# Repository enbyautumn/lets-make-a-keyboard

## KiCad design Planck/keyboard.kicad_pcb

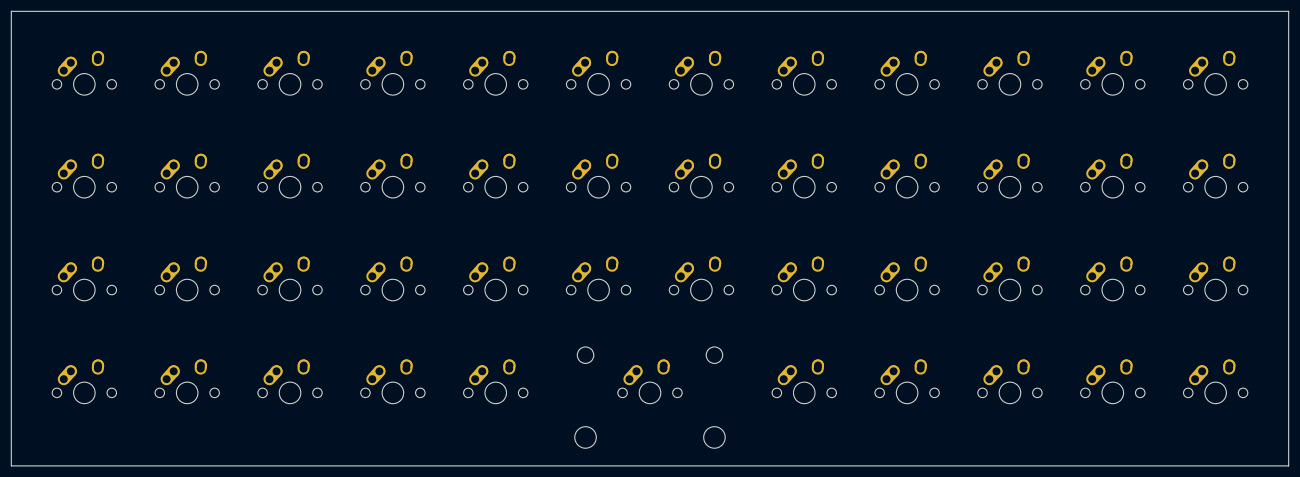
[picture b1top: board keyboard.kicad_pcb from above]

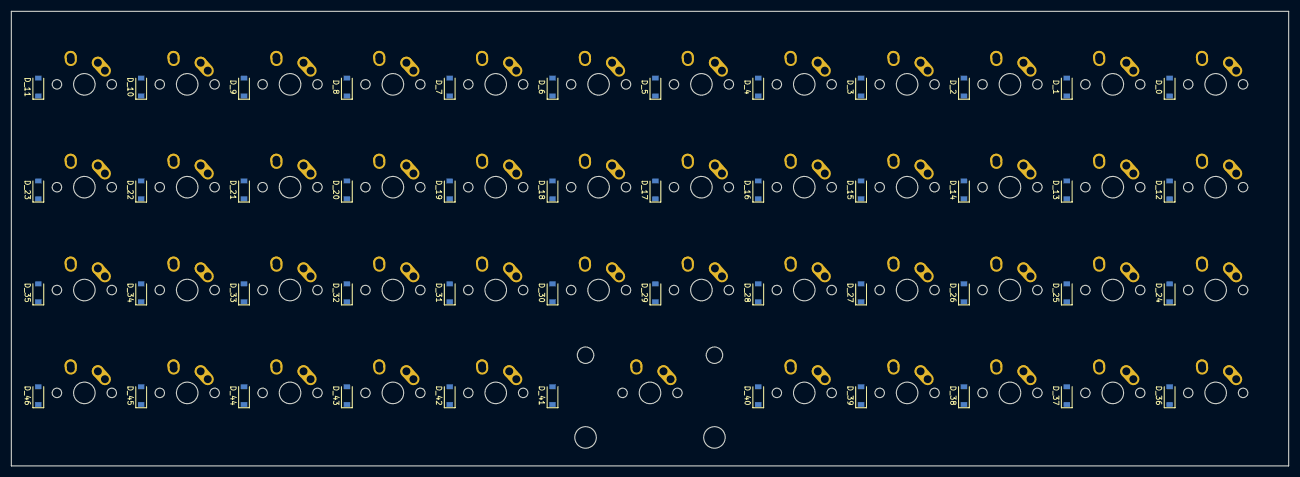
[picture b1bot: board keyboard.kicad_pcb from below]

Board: 2 copper layers, 236.6 x 84.2 mm, 94 parts (47 on the bottom side), 63 nets, no tracks yet.

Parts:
D_0, D_1, D_2, D_3, D_4, D_5, D_6, D_7, D_8, D_9, D_10, D_11, D_12, D_13, D_14, D_15, D_16, D_17, D_18, D_19, D_20, D_21, D_22, D_23, D_24, D_25, D_26, D_27, D_28, D_29, D_30, D_31, D_32, D_33, D_34, D_35, D_36, D_37, D_38, D_39, D_40, D_41, D_42, D_43, D_44, D_45, D_46: D; D_SOD-123
K_0, K_1, K_2, K_3, K_4, K_5, K_6, K_7, K_8, K_9, K_10, K_11, K_12, K_13, K_14, K_15, K_16, K_17, K_18, K_19, K_20, K_21, K_22, K_23, K_24, K_25, K_26, K_27, K_28, K_29, K_30, K_31, K_32, K_33, K_34, K_35, K_36, K_37, K_38, K_39, K_40, K_42, K_43, K_44, K_45, K_46: KEYSW; MX-1U-NoLED
K_41: KEYSW; MX-2U-NoLED

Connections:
unnamed: D_0.2, K_0.2
unnamed: D_1.2, K_1.2
unnamed: D_2.2, K_2.2
unnamed: D_3.2, K_3.2
unnamed: D_4.2, K_4.2
unnamed: D_5.2, K_5.2
unnamed: D_6.2, K_6.2
unnamed: D_7.2, K_7.2
unnamed: D_8.2, K_8.2
unnamed: D_9.2, K_9.2
unnamed: D_10.2, K_10.2
unnamed: D_11.2, K_11.2
unnamed: D_12.2, K_12.2
unnamed: D_13.2, K_13.2
unnamed: D_14.2, K_14.2
unnamed: D_15.2, K_15.2
unnamed: D_16.2, K_16.2
unnamed: D_17.2, K_17.2
unnamed: D_18.2, K_18.2
unnamed: D_19.2, K_19.2
unnamed: D_20.2, K_20.2
unnamed: D_21.2, K_21.2
unnamed: D_22.2, K_22.2
unnamed: D_23.2, K_23.2
unnamed: D_24.2, K_24.2
unnamed: D_25.2, K_25.2
unnamed: D_26.2, K_26.2
unnamed: D_27.2, K_27.2
unnamed: D_28.2, K_28.2
unnamed: D_29.2, K_29.2
unnamed: D_30.2, K_30.2
unnamed: D_31.2, K_31.2
unnamed: D_32.2, K_32.2
unnamed: D_33.2, K_33.2
unnamed: D_34.2, K_34.2
unnamed: D_35.2, K_35.2
unnamed: D_36.2, K_36.2
unnamed: D_37.2, K_37.2
unnamed: D_38.2, K_38.2
unnamed: D_39.2, K_39.2
unnamed: D_40.2, K_40.2
unnamed: D_41.2, K_41.2
unnamed: D_42.2, K_42.2
unnamed: D_43.2, K_43.2
unnamed: D_44.2, K_44.2
unnamed: D_45.2, K_45.2
unnamed: D_46.2, K_46.2
col0: K_0.1, K_12.1, K_24.1, K_36.1
col1: K_1.1, K_13.1, K_25.1, K_37.1
col2: K_2.1, K_14.1, K_26.1, K_38.1
col3: K_3.1, K_15.1, K_27.1, K_39.1
col4: K_4.1, K_16.1, K_28.1, K_40.1
col5: K_5.1, K_17.1, K_29.1
col6: K_6.1, K_18.1, K_30.1, K_41.1
col7: K_7.1, K_19.1, K_31.1, K_42.1
col8: K_8.1, K_20.1, K_32.1, K_43.1
col9: K_9.1, K_21.1, K_33.1, K_44.1
col10: K_10.1, K_22.1, K_34.1, K_45.1
col11: K_11.1, K_23.1, K_35.1, K_46.1
row0: D_0.1, D_1.1, D_2.1, D_3.1, D_4.1, D_5.1, D_6.1, D_7.1, D_8.1, D_9.1, D_10.1, D_11.1
row1: D_12.1, D_13.1, D_14.1, D_15.1, D_16.1, D_17.1, D_18.1, D_19.1, D_20.1, D_21.1, D_22.1, D_23.1
row2: D_24.1, D_25.1, D_26.1, D_27.1, D_28.1, D_29.1, D_30.1, D_31.1, D_32.1, D_33.1, D_34.1, D_35.1
row3: D_36.1, D_37.1, D_38.1, D_39.1, D_40.1, D_41.1, D_42.1, D_43.1, D_44.1, D_45.1, D_46.1

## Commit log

2021-06-14 hey sexy
